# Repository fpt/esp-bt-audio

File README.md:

# esp-bt-audio

Battery-powered Bluetooth headphone receiver. An iPhone streams over A2DP to an
ESP32-WROOM-32E, which drives a PT8211 I2S DAC and an LM4881 headphone amp.
One LiPo cell, charged over USB by a TP4056 module.

- Bluetooth Classic A2DP sink (SBC) + AVRCP (play/pause, phone absolute volume)
- Push-button soft power latch, battery monitor, automatic power-off
- WS2812B-V6 status LED
- Flashed through a 6-pin zig-zag header with an M5Stack ESP32-Downloader

## Boards

Two boards, connected by a 12-pin header (3V3, GND, BCLK, WS, DIN, MUTE, 3V3_EN, VDD).

| Directory | Board | Contents |
|---|---|---|
| `main/` | main | ESP32-WROOM-32E, power and BT buttons, LED, power latch (D1/D3), battery divider, programming header |
| `i2s/` | i2s-power | TP4056 module, RT9080 3.3 V LDO, PT8211, LM4881, 3.5 mm jack |

KiCad 10. Custom symbols and footprints (`MyLibrary:*`) come from the global library at
`../KiCad/MyLibrary.kicad_sym` / `../KiCad/MyLibrary.pretty`, not from this repo.

## Firmware

ESP-IDF v5.4 in Docker, see [firmware/README.md](firmware/README.md).

```bash
cd firmware
make build
make flash PORT=COM5
make monitor PORT=COM5
```

## Docs (Japanese)

- [docs/esp_bt_audio_receiver.md](docs/esp_bt_audio_receiver.md): whole-system design (power, pins, audio, controls, current budget, parts list)
- [docs/i2s_audio_design.md](docs/i2s_audio_design.md): PT8211 + LM4881 audio stage

## Layout

```
main/        main board (KiCad)
i2s/         i2s-power board (KiCad)
firmware/    ESP-IDF firmware
docs/        design notes
.claude/     Claude Code skills (vendored from aklofas/kicad-happy)
```

## Status

- **v0.1.0** (tag): first PCBs ordered (bare boards, hand assembly). Not yet tested.
- **Next batch** (`main`, ordered 2026-11-04): new pin assignment on i2s-power, both boards
  assembled by JLCPCB (Economic PCBA).
Firmware builds, not yet run on hardware.

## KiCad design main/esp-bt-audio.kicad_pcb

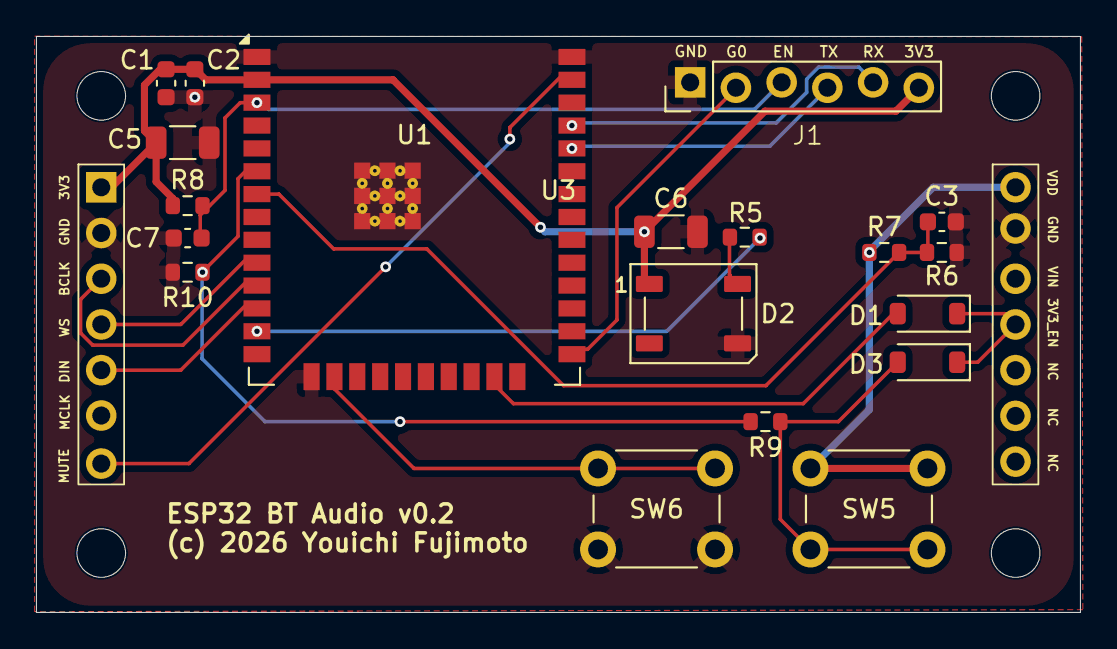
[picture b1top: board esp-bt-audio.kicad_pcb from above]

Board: 2 copper layers, 58.0 x 32.0 mm, 20 parts (0 on the bottom side), 19 nets.

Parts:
C1: 10u; C_0603_1608Metric
C2, C3: 100n; C_0603_1608Metric
C5, C6: 100u; C_1206_3216Metric
C7: 1u; C_0603_1608Metric
D1, D3: 1N4148W; D_SOD-123
D2: WS2812B-V6; LED_WS2812B_PLCC4_5.0x5.0mm_P3.2mm
J1: ESPWriterJig; ESP32-Downloader_Pins
R5: 220; R_0603_1608Metric
R6, R7, R10: 100k; R_0603_1608Metric
R8: 10k; R_0603_1608Metric
R9: 22k; R_0603_1608Metric
SW5: SW_PWR1; SW_PUSH_6mm
SW6: SW_BT1; SW_PUSH_6mm
U1: ESP32-WROOM-32E
U3: github.com_fpt-I2C-Power_Module

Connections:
+3V3: C1.1, C2.1, C5.1, C6.1, D2.1 (VDD), J1.6 (3V3), R8.1, U1.2 (VDD), U3.1 (3V3)
/3V3_EN: D1.1 (K), D3.1 (K), U3.11 (3V3_EN)
/BAT_SENSE: C3.1, R6.1, R7.2, U1.7 (IO35)
/BCLK: U1.11 (IO26), U3.3 (BCLK)
/BOOT: J1.2 (G0), U1.25 (IO0)
/BTN_A1: SW6.1, U1.16 (IO13)
/DATA: U1.12 (IO27), U3.5 (DIN)
/EN: C7.1, J1.3 (EN), R8.2, U1.3 (EN)
/ESP_RX: J1.4 (TX), U1.34 (RXD0/IO3)
/ESP_TX: J1.5 (RX), U1.35 (TXD0/IO1)
/PWR_BTN: R9.2, R10.1, U1.6 (IO34)
/PWR_EN: D1.2 (A), U1.23 (IO15)
/RGB_LED: R5.1, U1.13 (IO14)
/SHUTDOWN: U1.37 (IO23), U3.7 (MUTE)
/WS: U1.10 (IO25), U3.4 (WS)
GND: C1.2, C2.2, C3.2, C5.2, C6.2, C7.2, D2.3 (VSS), J1.1 (GND), R6.2, R10.2, SW6.2, U1.1 (GND), U1.15 (GND), U1.38 (GND), U1.39 (GND), U3.2 (GND), U3.13 (GND)
unnamed: D2.4 (DIN), R5.2
unnamed: D3.2 (A), R9.1, SW5.2
VDD: R7.1, SW5.1, U3.14 (VDD)

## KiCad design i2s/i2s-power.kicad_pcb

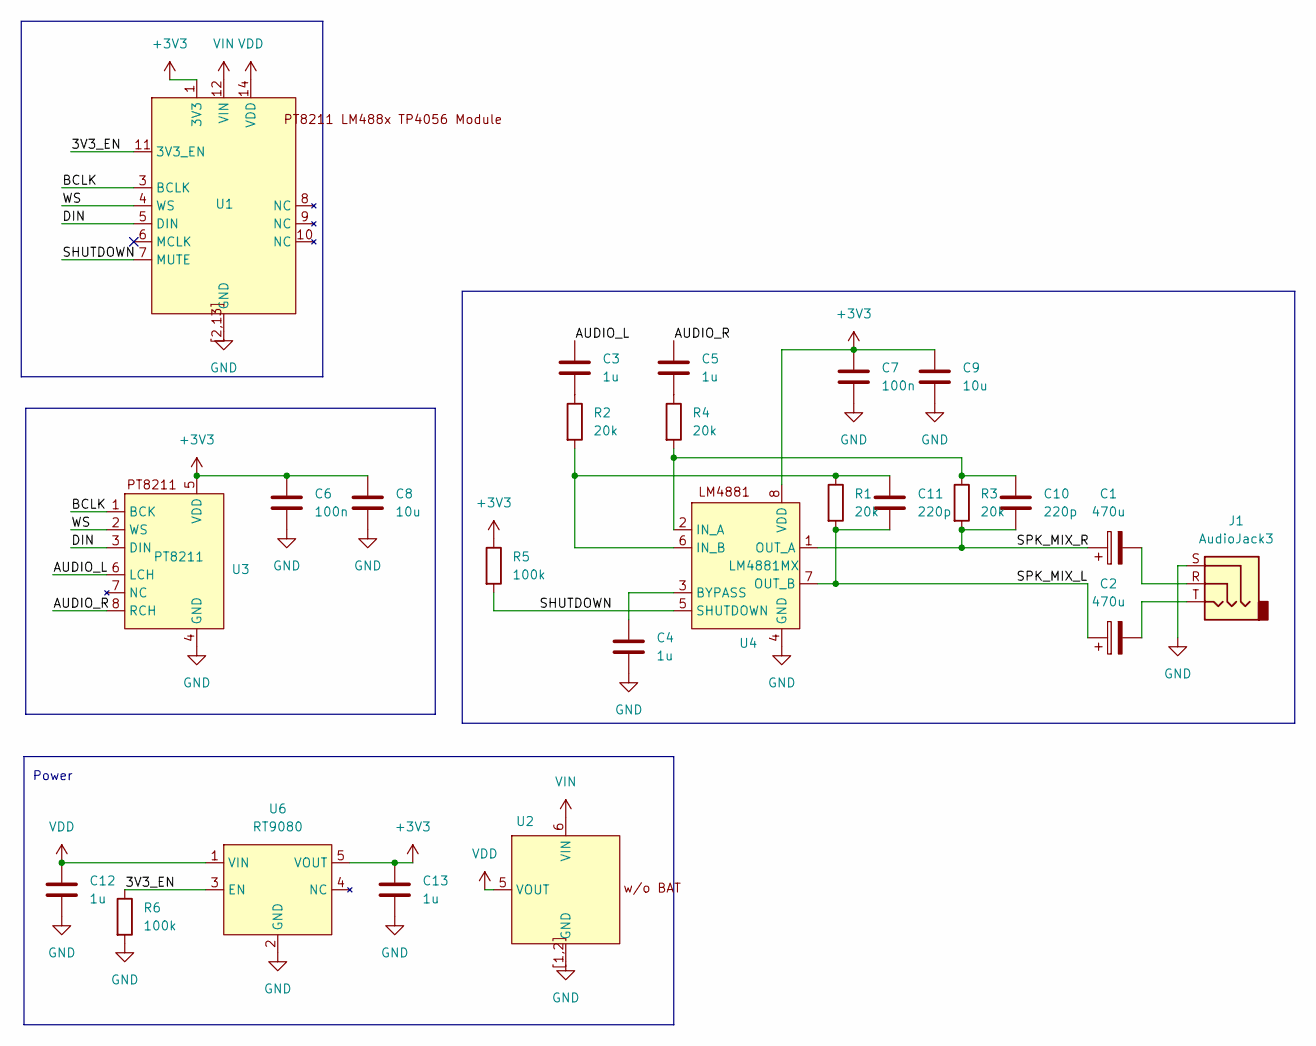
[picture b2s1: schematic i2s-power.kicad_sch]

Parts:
C1, C2: 470u; CP_Radial_D8.0mm_P3.50mm
C3, C4, C5, C12, C13: 1u; C_0603_1608Metric
C6, C7: 100n; C_0603_1608Metric
C8, C9: 10u; C_0603_1608Metric
C10, C11: 220p; C_0603_1608Metric
J1: AudioJack3; Jack_3.5mm_Switronic_ST-005-G_THT_Horizontal
R1, R2, R3, R4: 20k; R_0603_1608Metric
R5, R6: 100k; R_0603_1608Metric
U1: github.com_fpt-I2C-Power_Module
U2: GENERIC_TP4056_Module_wo_bat
U3: PT8211; SOP-8_3.76x4.96mm_P1.27mm; LCSC C92004
U4: LM4881MX; SO-8_3.9x4.9mm_P1.27mm
U6: RT9080; TSOT-23-5

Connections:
+3V3: C6.1, C7.1, C8.1, C9.1, C13.1, R5.1, U1.1 (3V3), U3.5 (VDD), U4.8 (VDD), U6.5 (VOUT)
/3V3_EN: R6.1, U1.11 (3V3_EN), U6.3 (EN)
/AUDIO_L: C3.1, U3.6 (LCH)
/AUDIO_R: C5.1, U3.8 (RCH)
/BCLK: U1.3 (BCLK), U3.1 (BCK)
/DIN: U1.5 (DIN), U3.3 (DIN)
/SHUTDOWN: R5.2, U1.7 (MUTE), U4.5 (SHUTDOWN)
/SPK_MIX_L: C2.1, C11.2, R1.2, U4.7 (OUT_B)
/SPK_MIX_R: C1.1, C10.2, R3.2, U4.1 (OUT_A)
/WS: U1.4 (WS), U3.2 (WS)
GND: C4.2, C6.2, C7.2, C8.2, C9.2, C12.2, C13.2, J1.S, R6.2, U1.2 (GND), U1.13 (GND), U1.[2,13] (GND), U2.1 (GND), U2.2 (GND), U2.[1,2] (GND), U3.4 (GND), U4.4 (GND), U6.2 (GND)
unnamed: C1.2, J1.R
unnamed: C2.2, J1.T
unnamed: C3.2, R2.1
unnamed: C5.2, R4.1
unnamed: C4.1, U4.3 (BYPASS)
unnamed: C10.1, R3.1, R4.2, U4.2 (IN_A)
unnamed: C11.1, R1.1, R2.2, U4.6 (IN_B)
VDD: C12.1, U1.14 (VDD), U2.5 (VOUT), U6.1 (VIN)
VIN: U1.12 (VIN), U2.6 (VIN)

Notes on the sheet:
Power

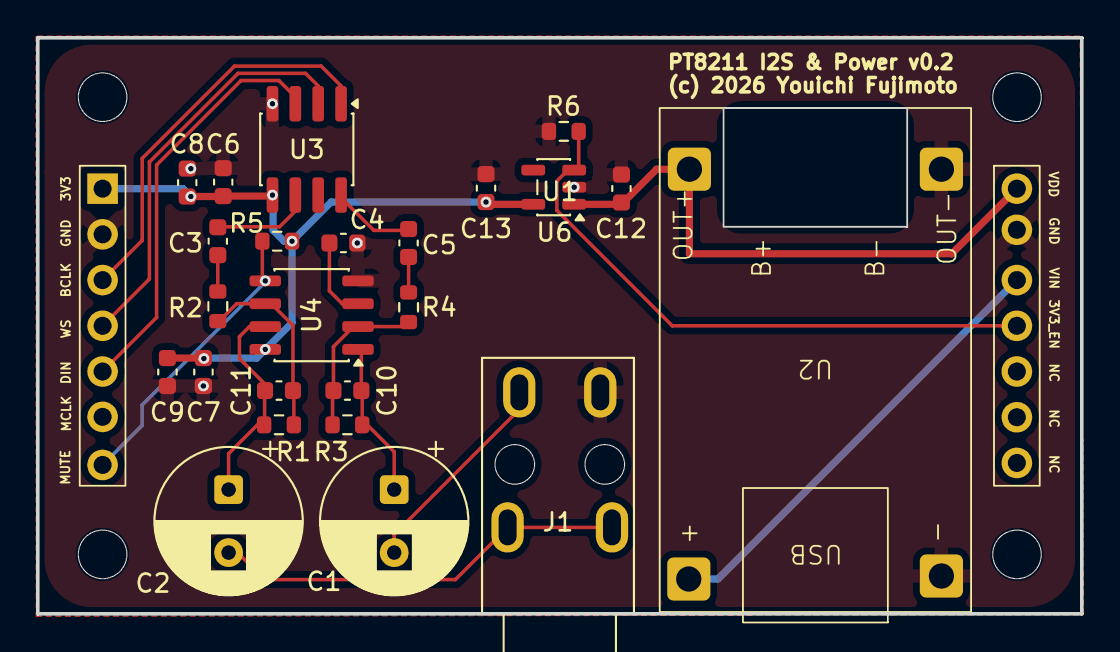
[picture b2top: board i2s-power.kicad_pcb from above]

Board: 2 copper layers, 58.0 x 32.0 mm, 25 parts (0 on the bottom side), 20 nets.

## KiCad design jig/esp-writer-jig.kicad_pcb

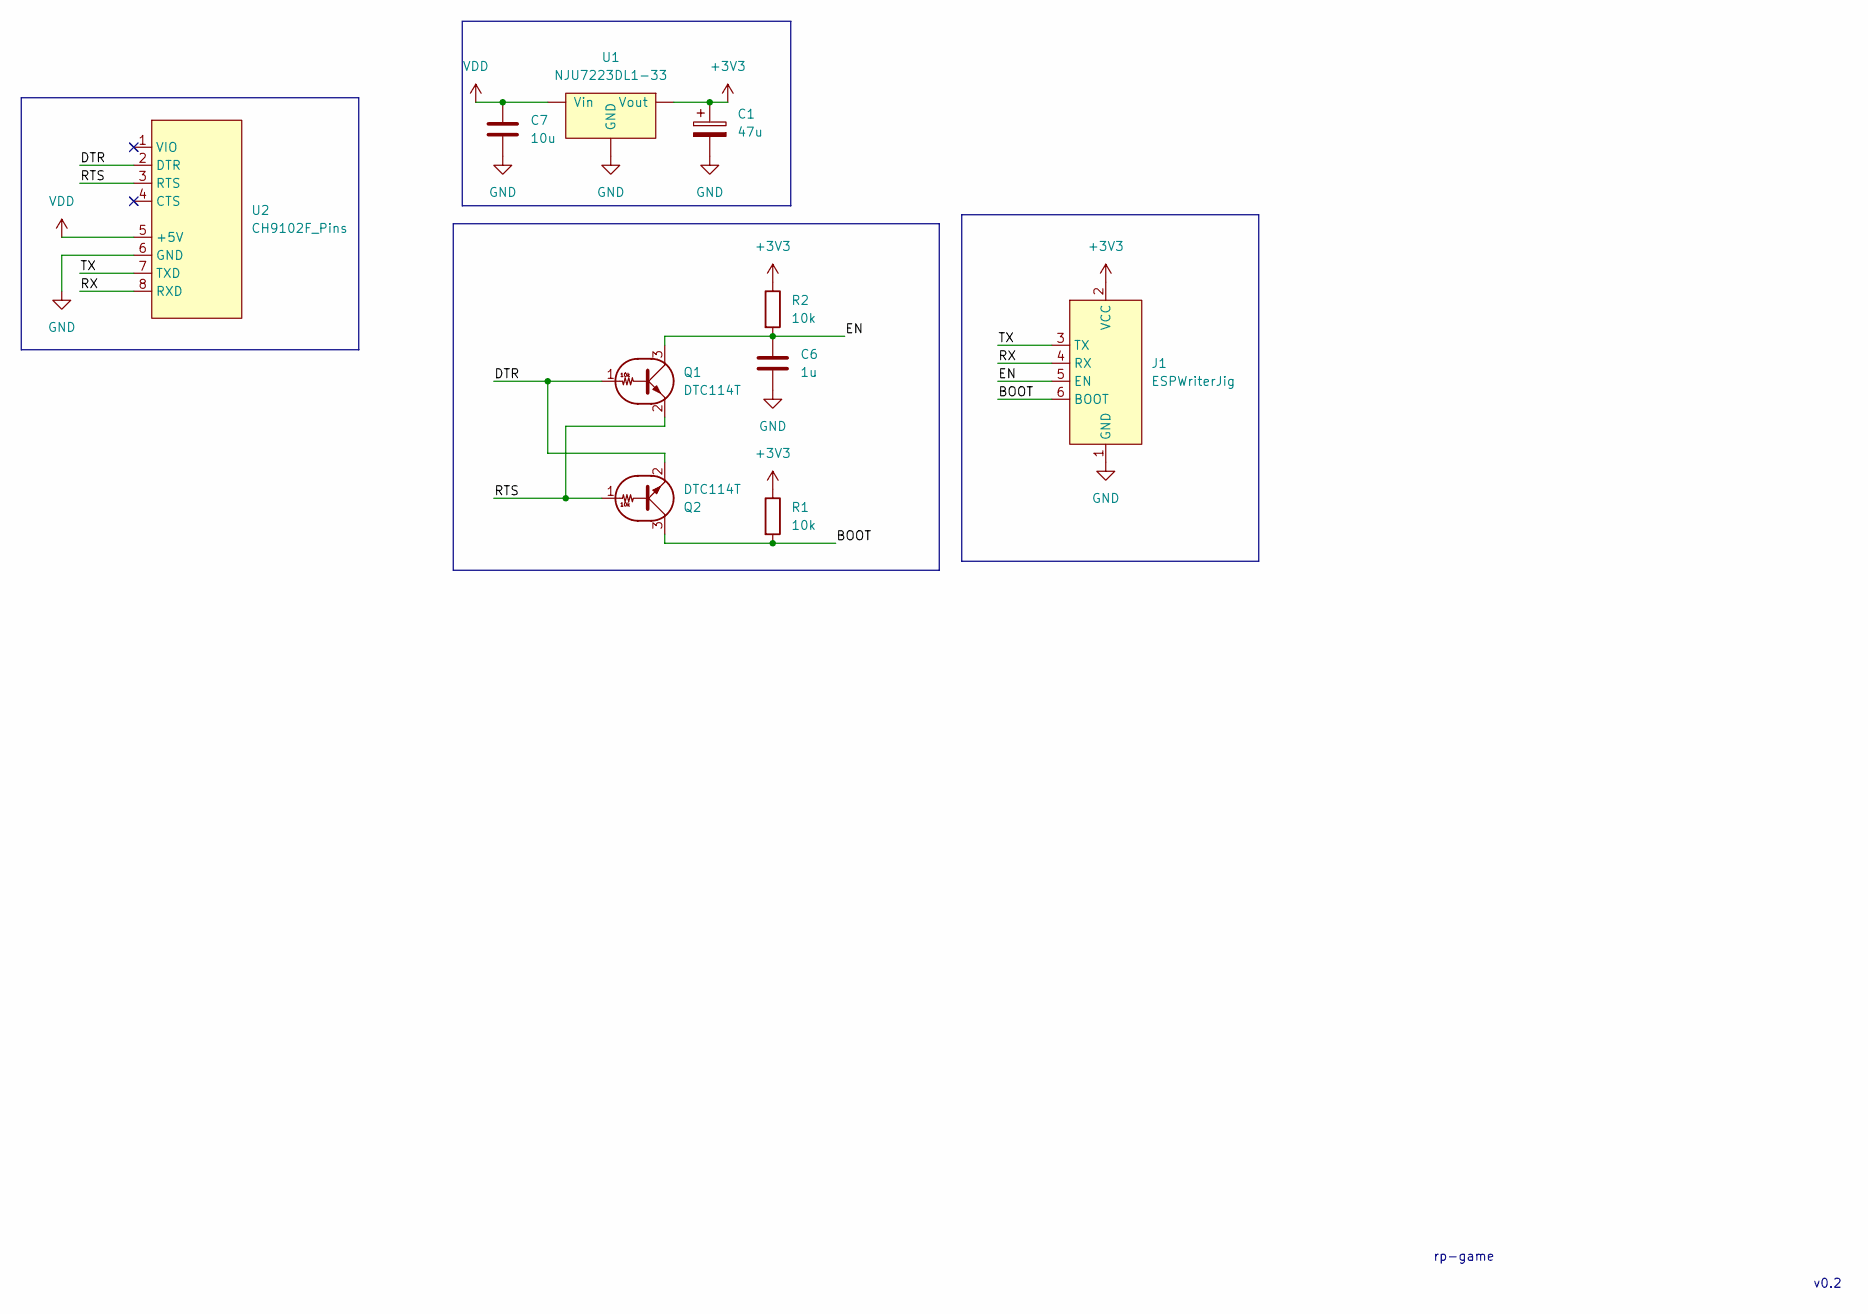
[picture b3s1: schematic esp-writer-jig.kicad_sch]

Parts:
C1: 47u; C_Radial_D5.0mm_H5.0mm_P2.00mm
C6: 1u; C_Disc_D5.0mm_W2.5mm_P5.00mm
C7: 10u; C_Disc_D5.0mm_W2.5mm_P5.00mm
J1: ESPWriterJig; ESPWriterJig_Pins
Q1, Q2: DTC114T; SOT-23-3
R1, R2: 10k; R_Axial_DIN0207_L6.3mm_D2.5mm_P7.62mm_Horizontal
U1: NJU7223DL1-33; TO-220-3_Vertical
U2: CH9102F_Pins; Aki_CH9102F_Pins

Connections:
+3V3: C1.1, J1.2 (VCC), R1.1, R2.1, U1.1 (Vout)
/BOOT: J1.6 (BOOT), Q2.3 (C), R1.2
/DTR: Q1.1 (B), Q2.2 (E), U2.2 (DTR)
/EN: C6.1, J1.5 (EN), Q1.3 (C), R2.2
/RTS: Q1.2 (E), Q2.1 (B), U2.3 (RTS)
/RX: J1.4 (RX), U2.8 (RXD)
/TX: J1.3 (TX), U2.7 (TXD)
GND: C1.2, C6.2, C7.2, J1.1 (GND), U1.3 (GND), U2.6 (GND)
VDD: C7.1, U1.2 (Vin), U2.5 (+5V)

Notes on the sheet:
v0.2
rp-game

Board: 2 copper layers, 10 parts (0 on the bottom side), 9 nets, no tracks yet.

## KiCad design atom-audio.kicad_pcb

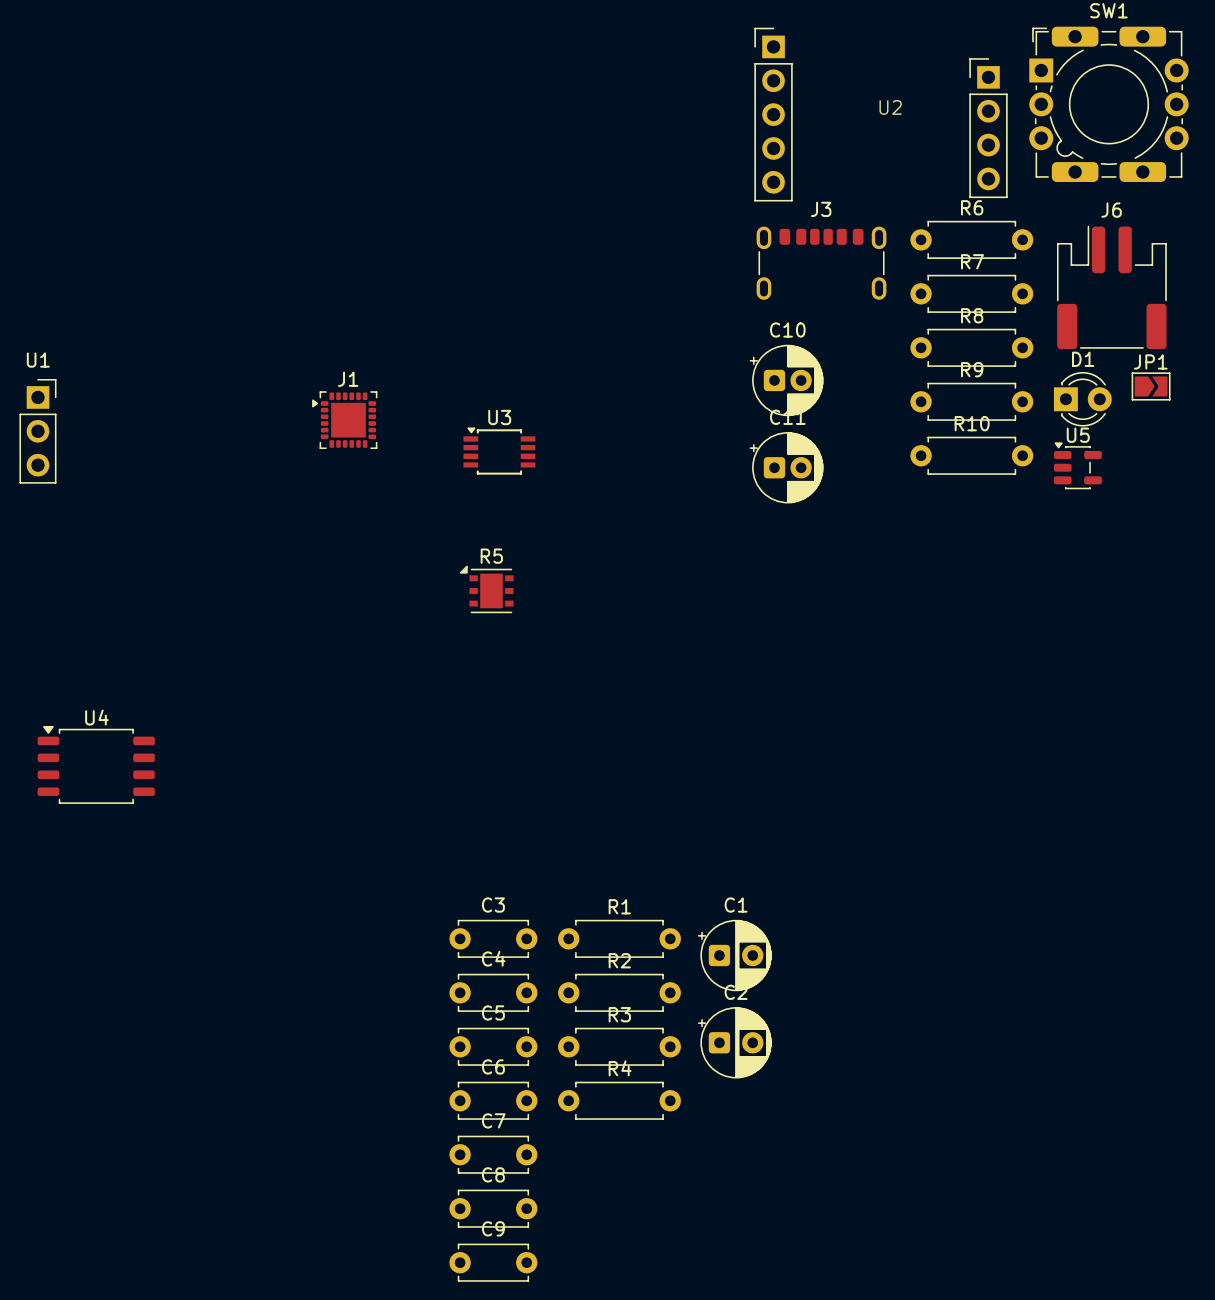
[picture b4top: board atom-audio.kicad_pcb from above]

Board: 2 copper layers, 32 parts (0 on the bottom side), 24 nets, no tracks yet.

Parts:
C1, C2: 470u; CP_Radial_D5.0mm_P2.50mm
C3, C5: 0.47u; C_Disc_D5.0mm_W2.5mm_P5.00mm
C4: 1u; C_Disc_D5.0mm_W2.5mm_P5.00mm
C6, C7: 0.1u; C_Disc_D5.0mm_W2.5mm_P5.00mm
C8, C9: 10u; C_Disc_D5.0mm_W2.5mm_P5.00mm
C10, C11: 10u; CP_Radial_D5.0mm_P2.00mm
D1: LED; LED_D3.0mm
J1: AudioJack3; TQFN-24-1EP_4x4mm_P0.5mm_EP2.6x2.6mm
J3: USB_C_Receptacle_PowerOnly_6P; USB_C_Receptacle_GCT_USB4125-xx-x-0190_6P_TopMnt_Horizontal
J6: Conn_01x02_Shielded; JST_PH_S2B-PH-SM4-TB_1x02-1MP_P2.00mm_Horizontal
JP1: SolderJumper_2_Open; SolderJumper-2_P1.3mm_Open_TrianglePad1.0x1.5mm
R1, R2, R3, R4: 20k; R_Axial_DIN0207_L6.3mm_D2.5mm_P7.62mm_Horizontal
R5: 100k; DFN-6-1EP_3x3mm_P0.95mm_EP1.7x2.6mm
R6, R7: 5k1; R_Axial_DIN0207_L6.3mm_D2.5mm_P7.62mm_Horizontal
R8: 4k7; R_Axial_DIN0207_L6.3mm_D2.5mm_P7.62mm_Horizontal
R9: 3k3; R_Axial_DIN0207_L6.3mm_D2.5mm_P7.62mm_Horizontal
R10: 1k; R_Axial_DIN0207_L6.3mm_D2.5mm_P7.62mm_Horizontal
SW1: SW_SPST; SW_NKK_NR01
U1: PinSocket_1x03_P2.54mm_Vertical
U2: M5Atom_Lite
U3: TSSOP-8_3x3mm_P0.65mm
U4: SOIC-8_5.3x5.3mm_P1.27mm
U5: MCP73831-2-OT; SOT-23-5

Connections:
+3V3: U1.1 (O), U2.1 (3V3)
/AUDIO_L: C3.1, U3.6 (LCH)
/AUDIO_R: C5.1, U3.8 (RCH)
/BCLK: U2.2 (G22), U3.1 (BCK)
/CHG_LED: D1.1 (K), U5.1 (STAT)
/DIN: U2.4 (G23), U3.3 (DIN)
/SHUTDOWN: R5.1, U4.5 (SHUTDOWN)
/WS: U2.3 (G19), U3.2 (WS)
GND: C4.2, C6.2, C7.2, C8.2, C9.2, C10.2, C11.2, J3.A12 (GND), J3.B12 (GND), J3.SH (SHIELD), J6.1, J6.MP (MountPin), JP1.1 (A), R5.2, R6.2, R7.2, R8.1, U1.2 (G), U3.4 (GND), U4.4 (GND), U5.2 (V_{SS})
unnamed: C3.2, R2.1
unnamed: C5.2, R4.1
unnamed: D1.2 (A), R10.1
unnamed: J3.A5 (CC1), R6.1
unnamed: J3.B5 (CC2), R7.1
unnamed: C11.1, J6.2, SW1.2 (B), U5.3 (V_{BAT})
unnamed: JP1.2 (B), R9.1
unnamed: C4.1, U4.3 (BYPASS)
unnamed: R3.1, R4.2, U4.2 (IN_A)
unnamed: R1.1, R2.2, U4.6 (IN_B)
unnamed: C1.1, R3.2, U4.1 (OUT_A)
unnamed: C2.1, R1.2, U4.7 (OUT_B)
unnamed: R8.2, R9.2, U5.5 (PROG)
VBUS: C10.1, J3.A9 (VBUS), J3.B9 (VBUS), R10.2, U5.4 (V_{DD})
VDD: C6.1, C7.1, C8.1, C9.1, SW1.1 (A), U1.3 (I), U3.5 (VDD), U4.8 (VDD)

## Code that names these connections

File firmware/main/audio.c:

/*
 * Decoded A2DP PCM -> I2S -> PT8211, and the LM4881 SHUTDOWN line.
 *
 * The A2DP sink data callback pushes PCM into a byte ring buffer without
 * blocking; audio_task applies the AVRCP volume and writes to I2S. The DMA
 * sends zeros (mid-scale on the PT8211) whenever the buffer runs dry.
 *
 * PT8211 is LSB-justified 16 bit. With 16-bit slots that is the same waveform as
 * MSB-justified, so the standard driver's MSB mode is used (BCK = 32 fs, no MCLK).
 *
 * The amp turns on when a stream starts and off CONFIG_BTR_AMP_OFF_DELAY_MS after
 * it stops, so short pauses don't click.
 */
#include <string.h>
#include "freertos/FreeRTOS.h"
#include "freertos/task.h"
#include "freertos/ringbuf.h"
#include "driver/i2s_std.h"
#include "driver/gpio.h"
#include "esp_check.h"
#include "esp_log.h"
#include "esp_timer.h"
#include "sdkconfig.h"
#include "app.h"

#define RINGBUF_SIZE  16384   /* ~90 ms at 44.1 kHz stereo */
#define CHUNK_MAX     2048

static const char *TAG = "audio";

static i2s_chan_handle_t s_tx;
static RingbufHandle_t s_rb;
static volatile uint32_t s_pending_rate;
static volatile uint16_t s_gain_q14 = 1 << 14;
static volatile bool s_streaming;
static volatile int64_t s_stop_us;    /* when the stream stopped, 0 = amp should stay as is */
static bool s_amp_on;
static uint32_t s_dropped;

static void amp_set(bool on)
{
    if (on != s_amp_on) {
        s_amp_on = on;
        gpio_set_level(CONFIG_BTR_AMP_SD_GPIO, on ? 0 : 1);
        ESP_LOGI(TAG, "amp %s", on ? "on" : "off");
    }
}

static void drain_ringbuf(void)
{
    size_t n;
    void *p;
    while ((p = xRingbufferReceiveUpTo(s_rb, &n, 0, RINGBUF_SIZE)) != NULL) {
        vRingbufferReturnItem(s_rb, p);
    }
}

static void process(int16_t *s, size_t samples)
{
    uint32_t g = s_gain_q14;
    for (size_t i = 0; i < samples; i += 2) {
        int32_t l = s[i], r = s[i + 1];
        if (g < (1 << 14)) {
            l = (l * (int32_t)g) >> 14;
            r = (r * (int32_t)g) >> 14;
        }
#ifdef CONFIG_BTR_SWAP_LR
        s[i] = (int16_t)r;
        s[i + 1] = (int16_t)l;
#else
        s[i] = (int16_t)l;
        s[i + 1] = (int16_t)r;
#endif
    }
}

static void apply_rate(uint32_t hz)
{
    i2s_std_clk_config_t clk = I2S_STD_CLK_DEFAULT_CONFIG(hz);
    i2s_channel_disable(s_tx);
    if (i2s_channel_reconfig_std_clock(s_tx, &clk) != ESP_OK) {
        ESP_LOGE(TAG, "rate %lu Hz failed", (unsigned long)hz);
    }
    i2s_channel_enable(s_tx);
    ESP_LOGI(TAG, "I2S %lu Hz", (unsigned long)hz);
}

static void audio_task(void *arg)
{
    static uint8_t chunk[CHUNK_MAX];
    for (;;) {
        uint32_t rate = s_pending_rate;
        if (rate) {
            s_pending_rate = 0;
            apply_rate(rate);
        }

        if (s_streaming) {
            amp_set(true);
        } else if (s_stop_us && esp_timer_get_time() - s_stop_us >= (int64_t)CONFIG_BTR_AMP_OFF_DELAY_MS * 1000) {
            s_stop_us = 0;
            amp_set(false);
        }

        size_t n = 0;
        uint8_t *p = xRingbufferReceiveUpTo(s_rb, &n, pdMS_TO_TICKS(50), CHUNK_MAX);
        if (!p) {
            continue;
        }
        /* Writes are whole stereo frames and the buffer size is a multiple of 4;
         * mask anyway so L/R never desync. */
        size_t len = n & ~(size_t)3;
        memcpy(chunk, p, len);
        vRingbufferReturnItem(s_rb, p);
        if (len == 0) {
            continue;
        }
        process((int16_t *)chunk, len / 2);
        size_t written;
        i2s_channel_write(s_tx, chunk, len, &written, portMAX_DELAY);
    }
}

esp_err_t audio_init(void)
{
    gpio_config_t io = {
        .pin_bit_mask = 1ULL << CONFIG_BTR_AMP_SD_GPIO,
        .mode = GPIO_MODE_OUTPUT,
    };
    gpio_set_level(CONFIG_BTR_AMP_SD_GPIO, 1);   /* amp in shutdown until audio */
    ESP_RETURN_ON_ERROR(gpio_config(&io), TAG, "amp gpio");

    i2s_chan_config_t chan = I2S_CHANNEL_DEFAULT_CONFIG(I2S_NUM_0, I2S_ROLE_MASTER);
    chan.auto_clear = true;   /* send zeros on underrun instead of repeating old data */
    ESP_RETURN_ON_ERROR(i2s_new_channel(&chan, &s_tx, NULL), TAG, "i2s channel");
    i2s_std_config_t std = {
        .clk_cfg = I2S_STD_CLK_DEFAULT_CONFIG(44100),
        .slot_cfg = I2S_STD_MSB_SLOT_DEFAULT_CONFIG(I2S_DATA_BIT_WIDTH_16BIT, I2S_SLOT_MODE_STEREO),
        .gpio_cfg = {
            .mclk = I2S_GPIO_UNUSED,
            .bclk = CONFIG_BTR_I2S_BCK_GPIO,
            .ws = CONFIG_BTR_I2S_WS_GPIO,
            .dout = CONFIG_BTR_I2S_DATA_GPIO,
            .din = I2S_GPIO_UNUSED,
        },
    };
    ESP_RETURN_ON_ERROR(i2s_channel_init_std_mode(s_tx, &std), TAG, "i2s std");
    ESP_RETURN_ON_ERROR(i2s_channel_enable(s_tx), TAG, "i2s enable");

    s_rb = xRingbufferCreate(RINGBUF_SIZE, RINGBUF_TYPE_BYTEBUF);
    if (!s_rb) {
        return ESP_ERR_NO_MEM;
    }
    if (xTaskCreate(audio_task, "audio", 3072, NULL, configMAX_PRIORITIES - 3, NULL) != pdPASS) {
        return ESP_ERR_NO_MEM;
    }
    return ESP_OK;
}

void audio_set_rate(uint32_t hz)
{
    s_pending_rate = hz;
}

void audio_set_volume(uint8_t vol)
{
    if (vol > 127) {
        vol = 127;
    }
    /* Square law: a rough perceptual taper, 127 -> unity. */
    s_gain_q14 = (uint16_t)(((uint32_t)vol * vol * (1 << 14)) / (127 * 127));
}

void audio_stream_event(bool started)
{
    s_streaming = started;
    if (started) {
        s_stop_us = 0;
    } else {
        s_stop_us = esp_timer_get_time();
        drain_ringbuf();
    }
}

void audio_feed(const uint8_t *buf, uint32_t len)
{
    if (!s_streaming) {
        return;
    }
    if (xRingbufferSend(s_rb, buf, len & ~3u, 0) != pdTRUE) {
        s_dropped += len;
    }
}

void audio_amp_off(void)
{
    s_streaming = false;
    s_stop_us = 0;
    amp_set(false);
}

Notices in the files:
i2s/i2s-power.kicad_pcb:
(c) 2026 Youichi Fujimoto
